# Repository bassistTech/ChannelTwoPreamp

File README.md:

# Channel Two Preamp

Compact bass preamp for adding second input to an existing amplifier

## Here's the prototype

## If you just want to read about it

Here's the [main design article for version 1](https://raw.githubusercontent.com/bassistTech/ChannelTwoPreamp/main/Docs/Channel%20Two%20Preamp.pdf).

## Important Files

This repository is my *entire project folder* so there are a lot of extraneous files. I've listed the most important ones here.

.\Modeling\Channel Two model circuit v1.asc = LTSpice modeling circuit

.\Docs\Build journal - v1.pdf = Build notes for version 1

.\Docs\Channel Two Preamp.ipynb = Main documentation for the project

.\KiCad project\Channel Two v2\Channel Two v2 BOM.csv = Bill of materials

.\KiCad project\Channel Two v2\CAM20241109\CAM20241109a.zip = Gerber files for upload to PCB manufacturer

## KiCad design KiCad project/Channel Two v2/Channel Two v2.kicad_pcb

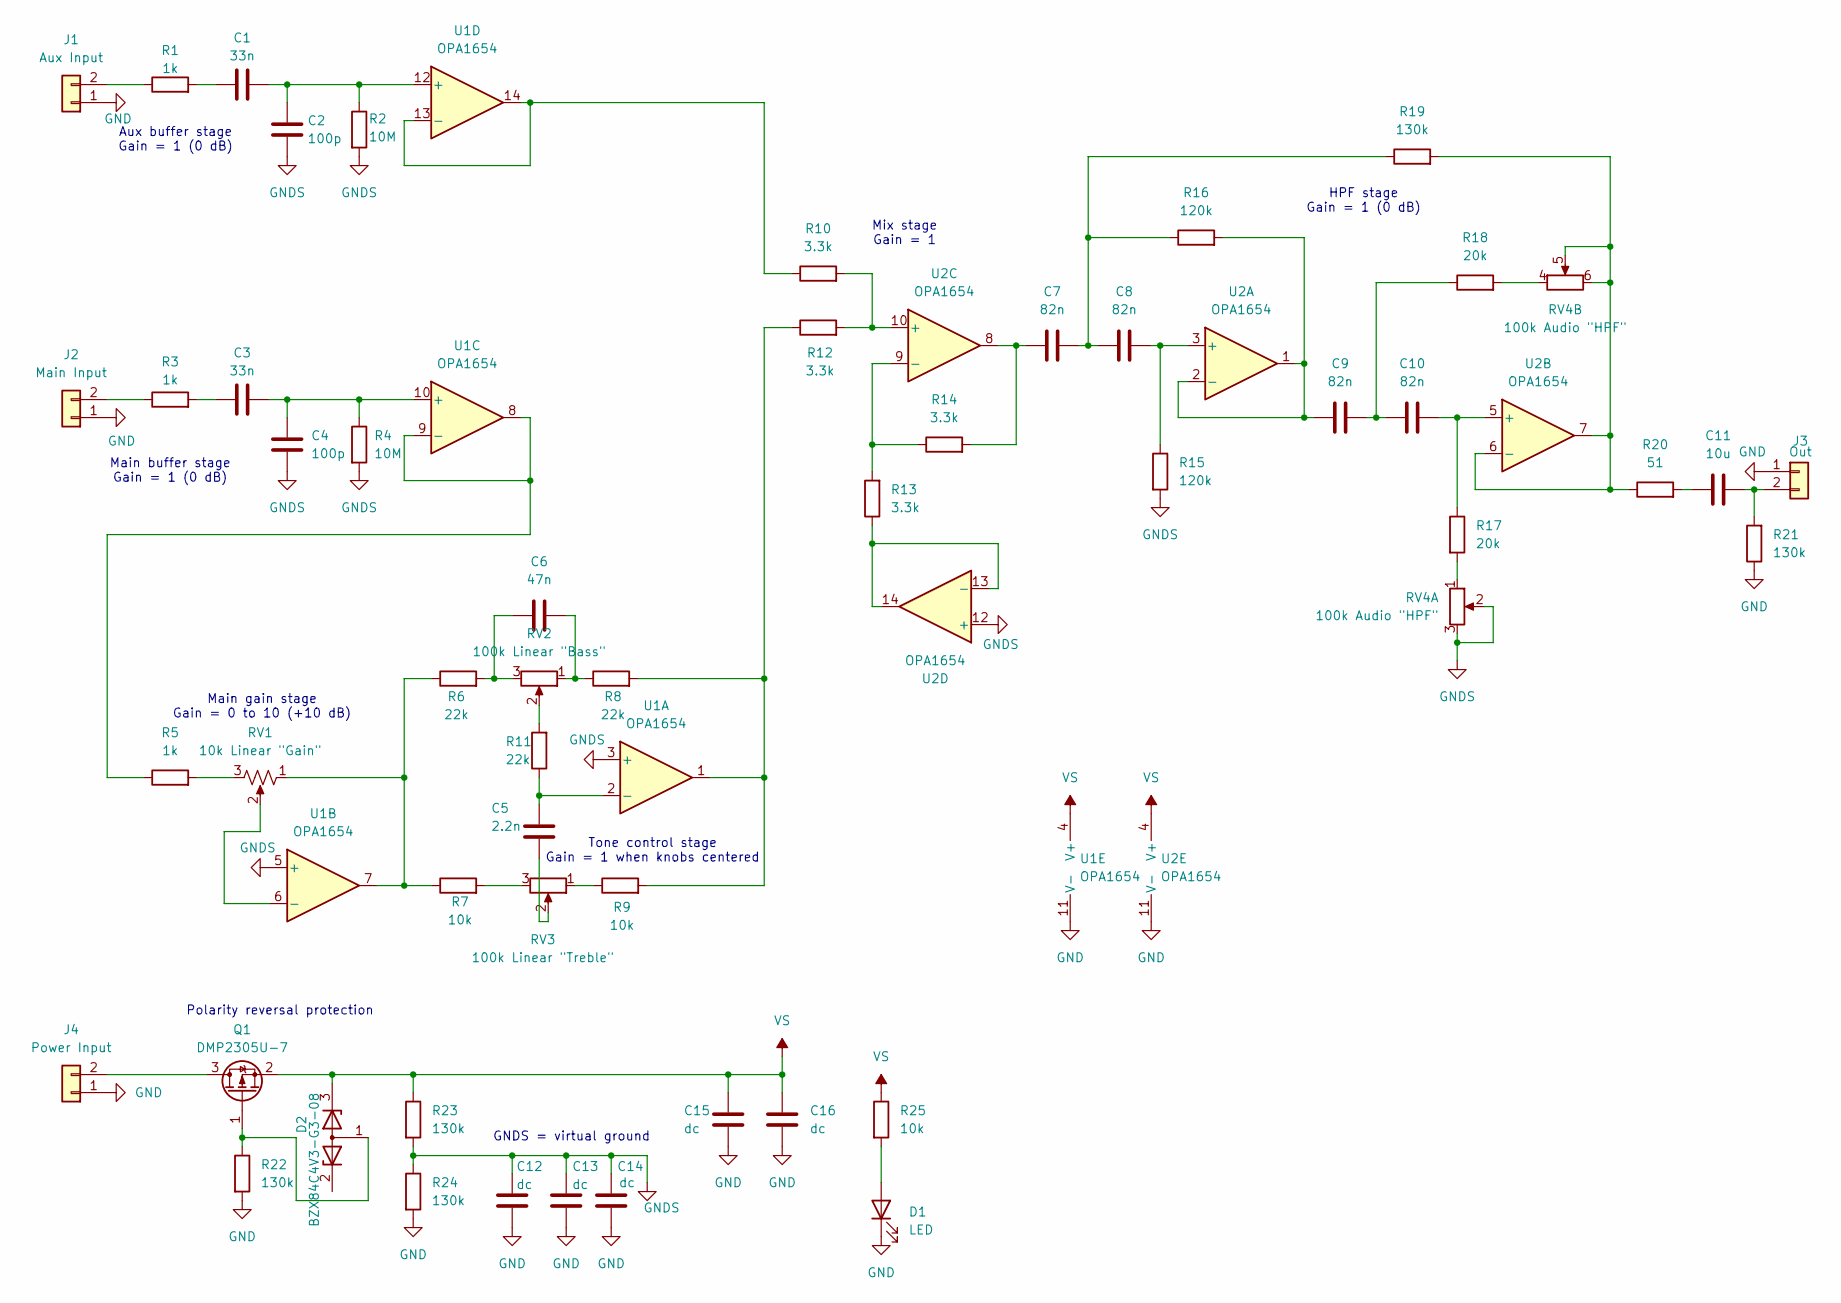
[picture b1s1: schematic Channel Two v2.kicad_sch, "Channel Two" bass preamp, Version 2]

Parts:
C1, C3: 33n; C_0805_2012Metric_Pad1.18x1.45mm_HandSolder
C2, C4: 100p; C_0805_2012Metric_Pad1.18x1.45mm_HandSolder
C5: 2.2n; C_0805_2012Metric_Pad1.18x1.45mm_HandSolder
C6: 47n; C_0805_2012Metric_Pad1.18x1.45mm_HandSolder
C7, C8, C9, C10: 82n; C_Rect_L7.0mm_W2.0mm_P5.00mm
C11: 10u; C_0805_2012Metric_Pad1.18x1.45mm_HandSolder
C12, C13, C14, C15, C16: dc; C_0805_2012Metric_Pad1.18x1.45mm_HandSolder
D1: LED; LED_D3.0mm
D2: BZX84C4V3-G3-08; TSOT-23_HandSoldering
J1: Aux Input; PinHeader_1x02_P2.00mm_Vertical
J2: Main Input; PinHeader_1x02_P2.00mm_Vertical
J3: Out; PinHeader_1x02_P2.00mm_Vertical
J4: Power Input; PinHeader_1x02_P2.00mm_Vertical
Q1: DMP2305U-7; TSOT-23_HandSoldering
R1, R3, R5: 1k; R_0805_2012Metric_Pad1.20x1.40mm_HandSolder
R2, R4: 10M; R_0805_2012Metric_Pad1.20x1.40mm_HandSolder
R6, R8, R11: 22k; R_0805_2012Metric_Pad1.20x1.40mm_HandSolder
R7, R9, R25: 10k; R_0805_2012Metric_Pad1.20x1.40mm_HandSolder
R10, R12, R13, R14: 3.3k; R_0805_2012Metric_Pad1.20x1.40mm_HandSolder
R15, R16: 120k; R_0805_2012Metric_Pad1.20x1.40mm_HandSolder
R17, R18: 20k; R_0805_2012Metric_Pad1.20x1.40mm_HandSolder
R19, R21, R22, R23, R24: 130k; R_0805_2012Metric_Pad1.20x1.40mm_HandSolder
R20: 51; R_0805_2012Metric_Pad1.20x1.40mm_HandSolder
RV1: 10k Linear "Gain"; Potentiometer_Alpha_RV120F
RV2: 100k Linear "Bass"; Potentiometer_Alpha_RV120F
RV3: 100k Linear "Treble"; Potentiometer_Alpha_RV120F
RV4: 100k Audio "HPF"; Potentiometer_Alpha_RV122F
U1, U2: OPA1654; TSSOP-14_4.4x5mm_P0.65mm

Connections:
GND: C12.2, C13.2, C14.2, C15.2, C16.2, D1.1 (K), J1.1, J2.1, J3.1, J4.1, R21.1, R22.2, R24.2, U1.11 (V-), U2.11 (V-)
GNDS: C2.2, C4.2, C12.1, C13.1, C14.1, R2.2, R4.2, R15.2, R23.2, R24.1, RV4.2, RV4.3, U1.3 (+), U1.5 (+), U2.12 (+)
unnamed: C1.1, R1.2
unnamed: C3.1, R3.2
unnamed: C5.2, RV3.2
unnamed: C6.1, R6.2, RV2.3
unnamed: C6.2, R8.1, RV2.1
unnamed: C7.1, R14.2, U2.8
unnamed: C7.2, C8.1, R16.1, R19.1
unnamed: C9.2, C10.1, R18.1
unnamed: C11.1, R20.2
unnamed: D1.2 (A), R25.2
unnamed: D2.1 (A), Q1.1 (G), R22.1
unnamed: J1.2, R1.1
unnamed: J2.2, R3.1
unnamed: C11.2, J3.2, R21.2
unnamed: J4.2, Q1.3 (D)
unnamed: R5.2, RV1.3
unnamed: R6.1, R7.1, RV1.1, U1.7
unnamed: R7.2, RV3.3
unnamed: R9.1, RV3.1
unnamed: R11.2, RV2.2
unnamed: R8.2, R9.2, R12.1, U1.1
unnamed: R17.2, RV4.1
unnamed: R18.2, RV4.4
unnamed: C5.1, R11.1, U1.2 (-)
unnamed: RV1.2, U1.6 (-)
unnamed: C3.2, C4.1, R4.1, U1.10 (+)
unnamed: R5.1, U1.8, U1.9 (-)
unnamed: C1.2, C2.1, R2.1, U1.12 (+)
unnamed: R10.1, U1.13 (-), U1.14
unnamed: C8.2, R15.1, U2.3 (+)
unnamed: C9.1, R16.2, U2.1, U2.2 (-)
unnamed: C10.2, R17.1, U2.5 (+)
unnamed: R19.2, R20.1, RV4.5, RV4.6, U2.6 (-), U2.7
unnamed: R10.2, R12.2, U2.10 (+)
unnamed: R13.2, R14.1, U2.9 (-)
unnamed: R13.1, U2.13 (-), U2.14
VS: C15.1, C16.1, D2.3 (K), Q1.2 (S), R23.1, R25.1, U1.4 (V+), U2.4 (V+)

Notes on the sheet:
Mix stage Gain = 1
Main buffer stage Gain = 1 (0 dB)
Polarity reversal protection
Tone control stage Gain = 1 when knobs centered
Aux buffer stage Gain = 1 (0 dB)
GNDS = virtual ground
HPF stage Gain = 1 (0 dB)
Main gain stage Gain = 0 to 10 (+10 dB)

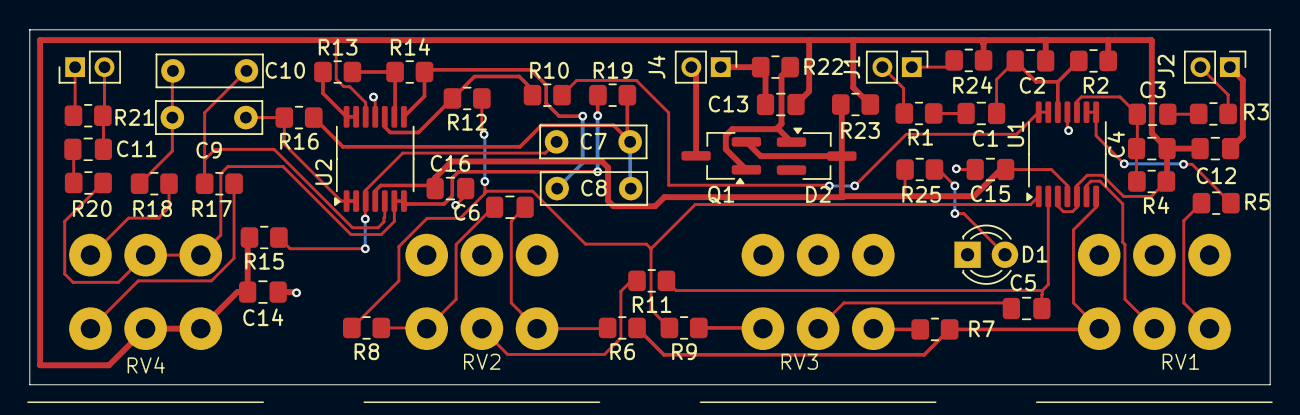
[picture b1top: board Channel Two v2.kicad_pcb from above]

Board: 2 copper layers, 84.3 x 24.1 mm, 54 parts (0 on the bottom side), 39 nets.

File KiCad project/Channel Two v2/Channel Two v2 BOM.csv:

"Reference","Value","Datasheet","Footprint","Qty","DNP"
"C1,C3","33n","~","Capacitor_SMD:C_0805_2012Metric_Pad1.18x1.45mm_HandSolder","2",""
"C2,C4","100p","~","Capacitor_SMD:C_0805_2012Metric_Pad1.18x1.45mm_HandSolder","2",""
"C5","2.2n","~","Capacitor_SMD:C_0805_2012Metric_Pad1.18x1.45mm_HandSolder","1",""
"C6","47n","~","Capacitor_SMD:C_0805_2012Metric_Pad1.18x1.45mm_HandSolder","1",""
"C7,C8,C9,C10","82n","~","Capacitor_THT:C_Rect_L7.0mm_W2.0mm_P5.00mm","4",""
"C11","10u","~","Capacitor_SMD:C_0805_2012Metric_Pad1.18x1.45mm_HandSolder","1",""
"C12,C13,C14,C15,C16","dc","~","Capacitor_SMD:C_0805_2012Metric_Pad1.18x1.45mm_HandSolder","5",""
"D1","LED","~","LED_THT:LED_D3.0mm","1",""
"D2","BZX84C4V3-G3-08","~","Package_TO_SOT_SMD:TSOT-23_HandSoldering","1",""
"J1","Aux Input","~","Connector_PinHeader_2.00mm:PinHeader_1x02_P2.00mm_Vertical","1",""
"J2","Main Input","~","Connector_PinHeader_2.00mm:PinHeader_1x02_P2.00mm_Vertical","1",""
"J3","Out","~","Connector_PinHeader_2.00mm:PinHeader_1x02_P2.00mm_Vertical","1",""
"J4","Power Input","~","Connector_PinHeader_2.00mm:PinHeader_1x02_P2.00mm_Vertical","1",""
"Q1","DMP2305U-7","~","Package_TO_SOT_SMD:TSOT-23_HandSoldering","1",""
"R1,R3,R5","1k","~","Resistor_SMD:R_0805_2012Metric_Pad1.20x1.40mm_HandSolder","3",""
"R2,R4","10M","~","Resistor_SMD:R_0805_2012Metric_Pad1.20x1.40mm_HandSolder","2",""
"R6,R8,R11","22k","~","Resistor_SMD:R_0805_2012Metric_Pad1.20x1.40mm_HandSolder","3",""
"R7,R9,R25","10k","~","Resistor_SMD:R_0805_2012Metric_Pad1.20x1.40mm_HandSolder","3",""
"R10,R12,R13,R14","3.3k","~","Resistor_SMD:R_0805_2012Metric_Pad1.20x1.40mm_HandSolder","4",""
"R15,R16","120k","~","Resistor_SMD:R_0805_2012Metric_Pad1.20x1.40mm_HandSolder","2",""
"R17,R18","20k","~","Resistor_SMD:R_0805_2012Metric_Pad1.20x1.40mm_HandSolder","2",""
"R19,R21,R22,R23,R24","130k","~","Resistor_SMD:R_0805_2012Metric_Pad1.20x1.40mm_HandSolder","5",""
"R20","51","~","Resistor_SMD:R_0805_2012Metric_Pad1.20x1.40mm_HandSolder","1",""
"RV1","10k Linear ""Gain""","~","FJD_HPF:Potentiometer_Alpha_RV120F","1",""
"RV2","100k Linear ""Bass""","~","FJD_HPF:Potentiometer_Alpha_RV120F","1",""
"RV3","100k Linear ""Treble""","~","FJD_HPF:Potentiometer_Alpha_RV120F","1",""
"RV4","100k Audio ""HPF""","~","FJD_HPF:Potentiometer_Alpha_RV122F","1",""
"U1,U2","OPA1654","http://www.ti.com/lit/ds/symlink/tlc274.pdf","Package_SO:TSSOP-14_4.4x5mm_P0.65mm","2",""

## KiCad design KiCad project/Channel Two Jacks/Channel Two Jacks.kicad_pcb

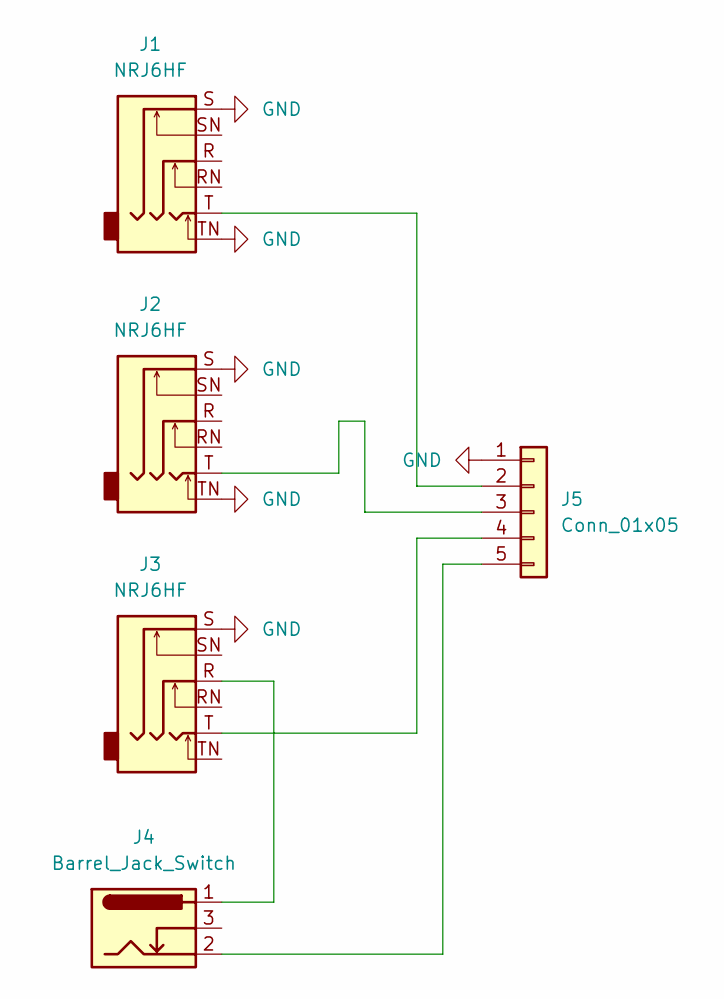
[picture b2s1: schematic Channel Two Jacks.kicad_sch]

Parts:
J1, J2, J3: NRJ6HF; Jack_6.35mm_Neutrik_NRJ6HF_Horizontal
J4: Barrel_Jack_Switch; BarrelJack_Kycon_KLDX-0202-xC_Horizontal
J5: Conn_01x05; PinHeader_1x05_P2.00mm_Vertical

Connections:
GND: J1.S, J1.TN, J2.S, J2.TN, J3.S, J5.1
unnamed: J3.R, J4.1
unnamed: J1.T, J5.2
unnamed: J2.T, J5.3
unnamed: J3.T, J5.4
unnamed: J4.2, J5.5

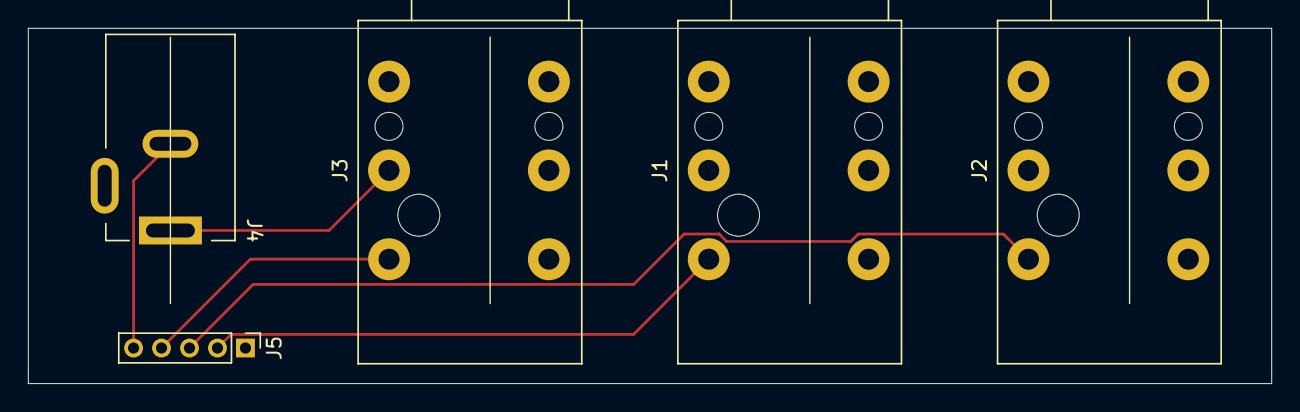
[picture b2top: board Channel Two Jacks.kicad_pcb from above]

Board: 2 copper layers, 88.9 x 25.4 mm, 5 parts (0 on the bottom side), 6 nets.

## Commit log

2024-11-03 First commit of files
2024-11-03 Documented R41 fix
2024-11-05 Mostly revision of the docs, some work on version 2
2024-11-05 Fixed link to main design file
2024-11-05 third try's the charm on this link
2024-11-05 Boy I'm having a great time at this
2024-11-17 Upload of version 2
2024-11-17 Gotta have a picture
2024-11-17 Fixed typo in readme
2024-11-20 Fixed links in design article and readme.md
2024-11-21 Fixed main document pdf
2024-11-21 Update note on potentiometers
